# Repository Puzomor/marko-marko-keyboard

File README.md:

# marko-marko-keyboard
Marko has a keyboard. Marko has a keyboard too.

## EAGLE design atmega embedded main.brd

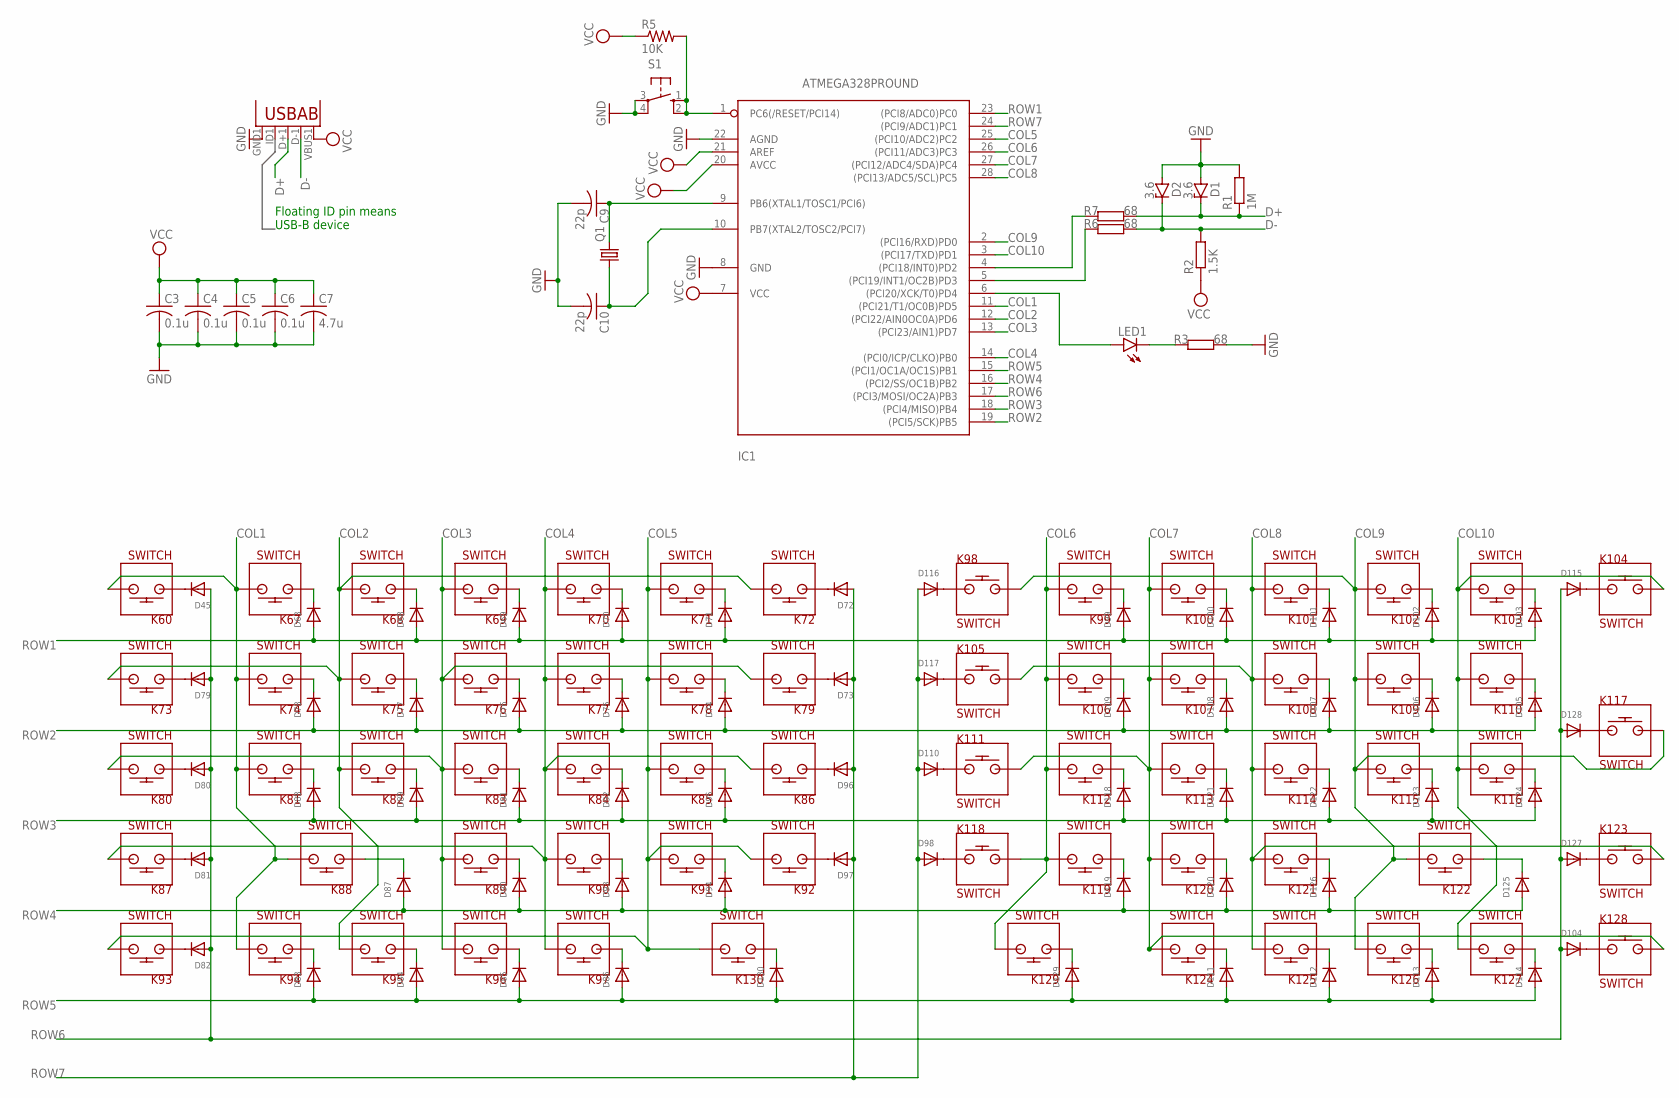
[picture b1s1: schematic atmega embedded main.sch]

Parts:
C3, C4, C5, C6: 0.1u; C0805
C7: 4.7u; C0805
C9, C10: 22p; C0805
D1, D2: 3.6; SMB
D45, D63, D68, D69, D70, D71, D72, D73, D74, D75, D76, D77, D78, D79, D80, D81, D82, D83, D84, D85, D86, D87, D88, D89, D90, D91, D92, D93, D94, D95, D96, D97, D98, D99, D100, D101, D102, D103, D104, D105, D106, D107, D108, D109, D110, D111, D112, D113, D114, D115, D116, D117, D118, D119, D120, D121, D122, D123, D124, D125, D126, D127, D128, D129, D130: DIODESMA; SMADIODE
IC1: ATMEGA328PROUND; DIL28-3-ROUND
K60, K67, K68, K69, K70, K71, K72, K73, K74, K75, K76, K77, K78, K79, K80, K81, K82, K83, K84, K85, K86, K87, K88, K89, K90, K91, K92, K93, K94, K95, K96, K97, K98, K99, K100, K101, K102, K103, K104, K105, K106, K107, K108, K109, K110, K111, K112, K113, K114, K115, K116, K117, K118, K119, K120, K121, K122, K123, K124, K125, K126, K127, K128, K129, K130: SWITCH; KAILH_LOW_PROFILE
LED1: LEDCHIPLED_1206; CHIPLED_1206
Q1: CRYSTALHC49S; HC49/S
R1: 1M; R1206
R2: 1.5K; R1206
R3, R6, R7: 68; R1206
R5: 10K; M0805
S1: 10-XX; B3F-10XX
U1: USB""; USB-MICRO-SMD

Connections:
COL1: IC1.11 ((PCI21/T1/OC0B)PD5), K60.P$2, K67.P$2, K74.P$2, K81.P$2, K88.P$2, K94.P$2
COL2: IC1.12 ((PCI22/AIN0OC0A)PD6), K68.P$2, K72.P$2, K73.P$2, K75.P$2, K82.P$2, K95.P$2
COL3: IC1.13 ((PCI23/AIN1)PD7), K69.P$2, K76.P$2, K79.P$2, K80.P$2, K83.P$2, K89.P$2, K96.P$2
COL4: IC1.14 ((PCI0/ICP/CLKO)PB0), K70.P$2, K77.P$2, K84.P$2, K86.P$2, K87.P$2, K90.P$2, K97.P$2
COL5: IC1.25 ((PCI10/ADC2)PC2), K71.P$2, K78.P$2, K85.P$2, K91.P$2, K92.P$2, K93.P$2, K130.P$2
COL6: IC1.26 ((PCI11/ADC3)PC3), K99.P$2, K106.P$2, K112.P$2, K118.P$2, K119.P$2, K129.P$2
COL7: IC1.27 ((PCI12/ADC4/SDA)PC4), K100.P$2, K107.P$2, K111.P$2, K113.P$2, K120.P$2, K124.P$2, K128.P$2
COL8: IC1.28 ((PCI13/ADC5/SCL)PC5), K101.P$2, K105.P$2, K108.P$2, K114.P$2, K121.P$2, K123.P$2, K125.P$2
COL9: IC1.2 ((PCI16/RXD)PD0), K98.P$2, K102.P$2, K109.P$2, K115.P$2, K117.P$2, K122.P$2, K126.P$2
COL10: IC1.3 ((PCI17/TXD)PD1), K103.P$2, K104.P$2, K110.P$2, K116.P$2, K127.P$2
D+: D1.C, R1.1, R7.2, U1.D+1 (D+)
D-: D2.C, R2.2, R6.2, U1.D-1 (D-)
GND: C3.2, C4.2, C5.2, C6.2, C7.2, C9.2, C10.2, D1.A, D2.A, IC1.8 (GND), IC1.22 (AGND), R1.2, R3.2, S1.3, S1.4 (P1), U1.GND1 (GND)
unnamed: D45.C, K60.P$1
unnamed: D79.C, K73.P$1
unnamed: D80.C, K80.P$1
unnamed: D81.C, K87.P$1
unnamed: D82.C, K93.P$1
unnamed: D63.C, K67.P$1
unnamed: D88.C, K81.P$1
unnamed: D78.C, K74.P$1
unnamed: D83.C, K94.P$1
unnamed: D77.C, K75.P$1
unnamed: D89.C, K82.P$1
unnamed: D68.C, K68.P$1
unnamed: D84.C, K95.P$1
unnamed: D76.C, K76.P$1
unnamed: IC1.1 (PC6(/RESET/PCI14)), R5.2, S1.1 (S), S1.2 (S1)
unnamed: C9.1, IC1.9 (PB6(XTAL1/TOSC1/PCI6)), Q1.2
unnamed: C10.1, IC1.10 (PB7(XTAL2/TOSC2/PCI7)), Q1.1
unnamed: D69.C, K69.P$1
unnamed: D90.C, K89.P$1
unnamed: D85.C, K96.P$1
unnamed: IC1.4 ((PCI18/INT0)PD2), R7.1
unnamed: D91.C, K83.P$1
unnamed: D86.C, K97.P$1
unnamed: D70.C, K70.P$1
unnamed: D75.C, K77.P$1
unnamed: D129.C, K129.P$1
unnamed: D116.C, K98.P$1
unnamed: D117.C, K105.P$1
unnamed: D92.C, K84.P$1
unnamed: D93.C, K90.P$1
unnamed: D94.C, K91.P$1
unnamed: D71.C, K71.P$1
unnamed: D74.C, K78.P$1
unnamed: D95.C, K85.P$1
unnamed: D130.C, K130.P$1
unnamed: D72.C, K72.P$1
unnamed: D73.C, K79.P$1
unnamed: D96.C, K86.P$1
unnamed: D97.C, K92.P$1
unnamed: D110.C, K111.P$1
unnamed: D98.C, K118.P$1
unnamed: D115.C, K104.P$1
unnamed: D119.C, K119.P$1
unnamed: D99.C, K99.P$1
unnamed: D109.C, K106.P$1
unnamed: D118.C, K112.P$1
unnamed: D111.C, K124.P$1
unnamed: D100.C, K100.P$1
unnamed: D108.C, K107.P$1
unnamed: D121.C, K113.P$1
unnamed: D120.C, K120.P$1
unnamed: D126.C, K121.P$1
unnamed: D101.C, K101.P$1
unnamed: D107.C, K108.P$1
unnamed: D122.C, K114.P$1
unnamed: D112.C, K125.P$1
unnamed: D123.C, K115.P$1
unnamed: D106.C, K109.P$1
unnamed: D102.C, K102.P$1
unnamed: D113.C, K126.P$1
unnamed: D124.C, K116.P$1
unnamed: D105.C, K110.P$1
unnamed: D103.C, K103.P$1
unnamed: D114.C, K127.P$1
unnamed: D128.C, K117.P$1
unnamed: D127.C, K123.P$1
unnamed: D104.C, K128.P$1
unnamed: IC1.5 ((PCI19/INT1/OC2B)PD3), R6.1
unnamed: IC1.6 ((PCI20/XCK/T0)PD4), LED1.A
unnamed: LED1.C, R3.1
unnamed: D87.C, K88.P$1
unnamed: D125.C, K122.P$1
ROW1: D63.A, D68.A, D69.A, D70.A, D71.A, D99.A, D100.A, D101.A, D102.A, D103.A, IC1.23 ((PCI8/ADC0)PC0)
ROW2: D74.A, D75.A, D76.A, D77.A, D78.A, D105.A, D106.A, D107.A, D108.A, D109.A, IC1.19 ((PCI5/SCK)PB5)
ROW3: D88.A, D89.A, D91.A, D92.A, D95.A, D118.A, D121.A, D122.A, D123.A, D124.A, IC1.18 ((PCI4/MISO)PB4)
ROW4: D87.A, D90.A, D93.A, D94.A, D119.A, D120.A, D125.A, D126.A, IC1.16 ((PCI2/SS/OC1B)PB2)
ROW5: D83.A, D84.A, D85.A, D86.A, D111.A, D112.A, D113.A, D114.A, D129.A, D130.A, IC1.15 ((PCI1/OC1A/OC1S)PB1)
ROW6: D45.A, D79.A, D80.A, D81.A, D82.A, D104.A, D115.A, D127.A, D128.A, IC1.17 ((PCI3/MOSI/OC2A)PB3)
ROW7: D72.A, D73.A, D96.A, D97.A, D98.A, D110.A, D116.A, D117.A, IC1.24 ((PCI9/ADC1)PC1)
VCC: C3.1, C4.1, C5.1, C6.1, C7.1, IC1.7 (VCC), IC1.20 (AVCC), IC1.21 (AREF), R2.1, R5.1, U1.VBUS1 (VBUS)

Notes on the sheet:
Floating ID pin means USB-B device

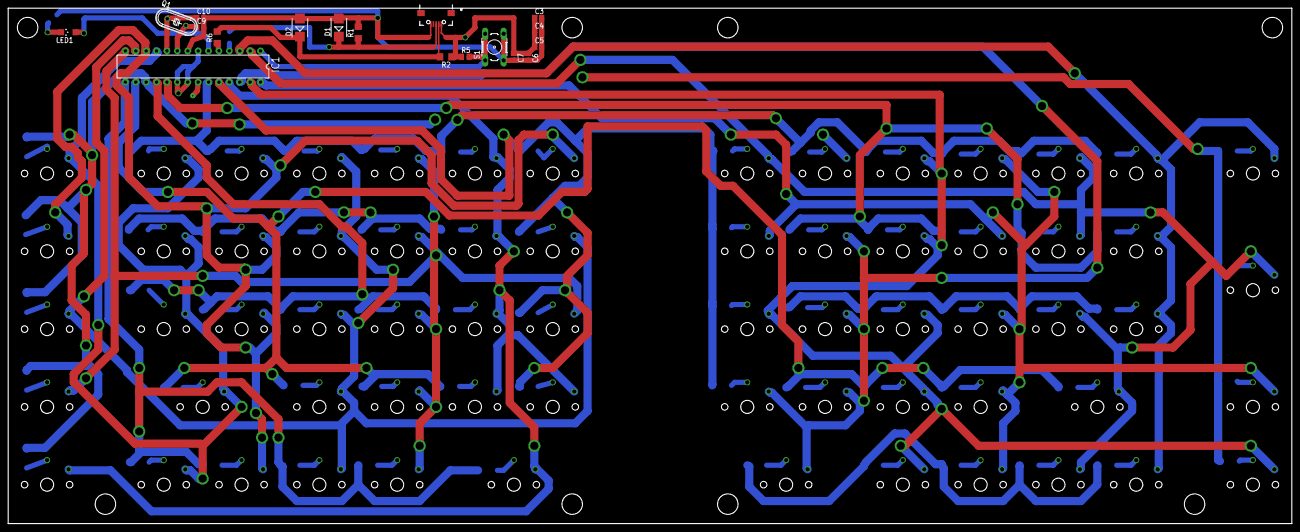
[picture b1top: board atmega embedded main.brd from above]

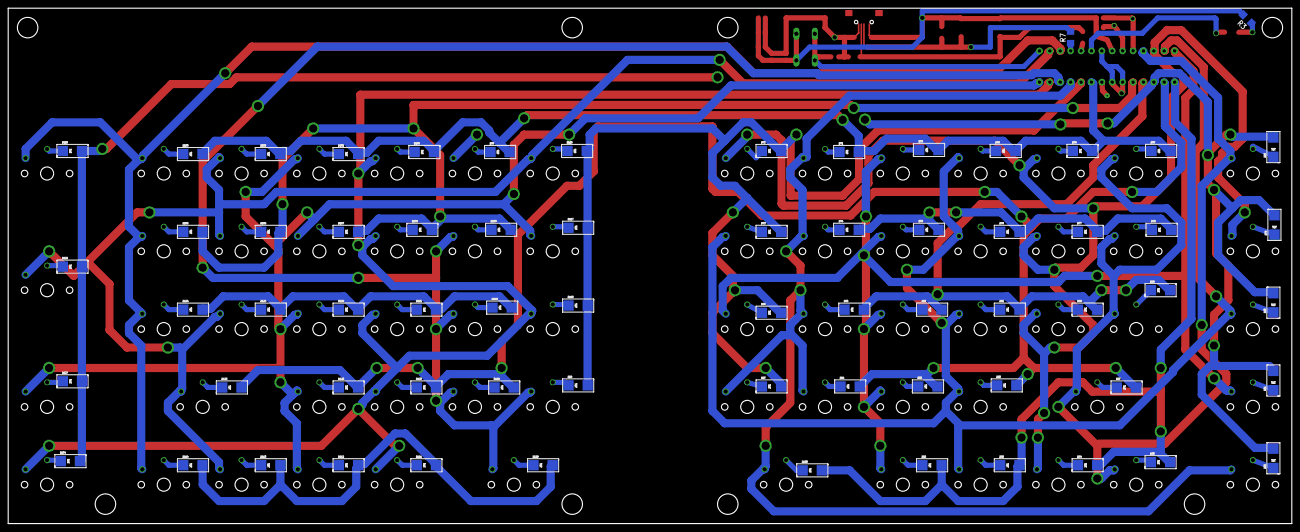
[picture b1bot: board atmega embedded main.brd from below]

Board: 2 copper layers, 313.5 x 125.9 mm, 150 parts (132 on the bottom side), 93 nets.

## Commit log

2017-11-26 initial files added
2017-11-26 fuck
2017-11-26 added libs
2017-12-28 Replaced chip with Atmege328p and made some other adjustments to the schematic
2017-12-30 Added an alternative wiring with fake rows for a chip with fewer pins
2017-12-31 Traced stuff
2018-01-01 Flipped switches and rewired everything
2018-01-01 Compacted stuff around the chip
2018-01-02 Started work on Marko's keyboard
2018-01-04 Fixed errors and made adjustments for USB
2018-01-07 Finalized logic and started work on Marko's layout
2018-01-08 Finished Marko's board and fixed some errors.
2018-01-08 Deleted old board.
2018-01-16 Wired up connectors
2018-01-16 Rewired some stuff
2018-01-29 Printed to PDF
2018-03-09 Bigger holes and traces for drilling
2020-05-24 Test 1
2020-05-24 Test2
2020-05-25 CNC stuff V1. Includes shitty pcb program, and key legends.
2020-05-28 Horrible design
2020-05-28 Less horrible
2020-05-29 Key legends and stuff
2020-05-29 Everything should be done in cnc-alu
2020-05-29 Made dxfs to cut
2020-05-30 Saved stuff in 2013 format
2020-05-30 Added cb files
2020-05-30 Kez legends to cut
2020-05-30 Less Horrible for Marko no.1
